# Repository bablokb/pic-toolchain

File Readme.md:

PIC Toolchain
=============

This is a collection of notes, sources and tools for a complete
PIC toolchain for the Raspbian operating-system.

Toolset
=======

To compile, link and flash PIC code, you need on software-side

  - a compiler (SDCC)
  - an assembler and linker (gputils)
  - a flasher

The first two programs are available for Raspbian, but it is recommended
to build both programs from source. For flashing, you need the 
program `pk2cmd`. You can find a precompiled version for armv6l in
`files/usr/local/bin`.

Example Programs
================

The directory `projects` contains a number of sample projects.
You must copy (install) the rule-files `projects/ptc_rules*.inc`
(generic makefile-rules) to a system-include directory automatically
searched by `make`, e.g. `/usr/local/include` or add the `-I dir` option
to the invocation of `make`.

The directory `projects/include` contains `.h`-files (c-includes)
used by all projects. You should also copy (install) these files to
`/usr/local/include` if you want to use these files in other projects.

The projects demonstrate various aspects, e.g. how to embbed assembler code
into C-code, or link with preexisting assembler-code.

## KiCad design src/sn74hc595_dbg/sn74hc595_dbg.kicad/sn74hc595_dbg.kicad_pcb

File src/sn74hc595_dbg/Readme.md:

SN74HC595 based debugger for the PIC12F675
==========================================

This project has moved to [https://github.com/bablokb/pic-sn74hc595](https://github.com/bablokb/pic-sn74hc595).

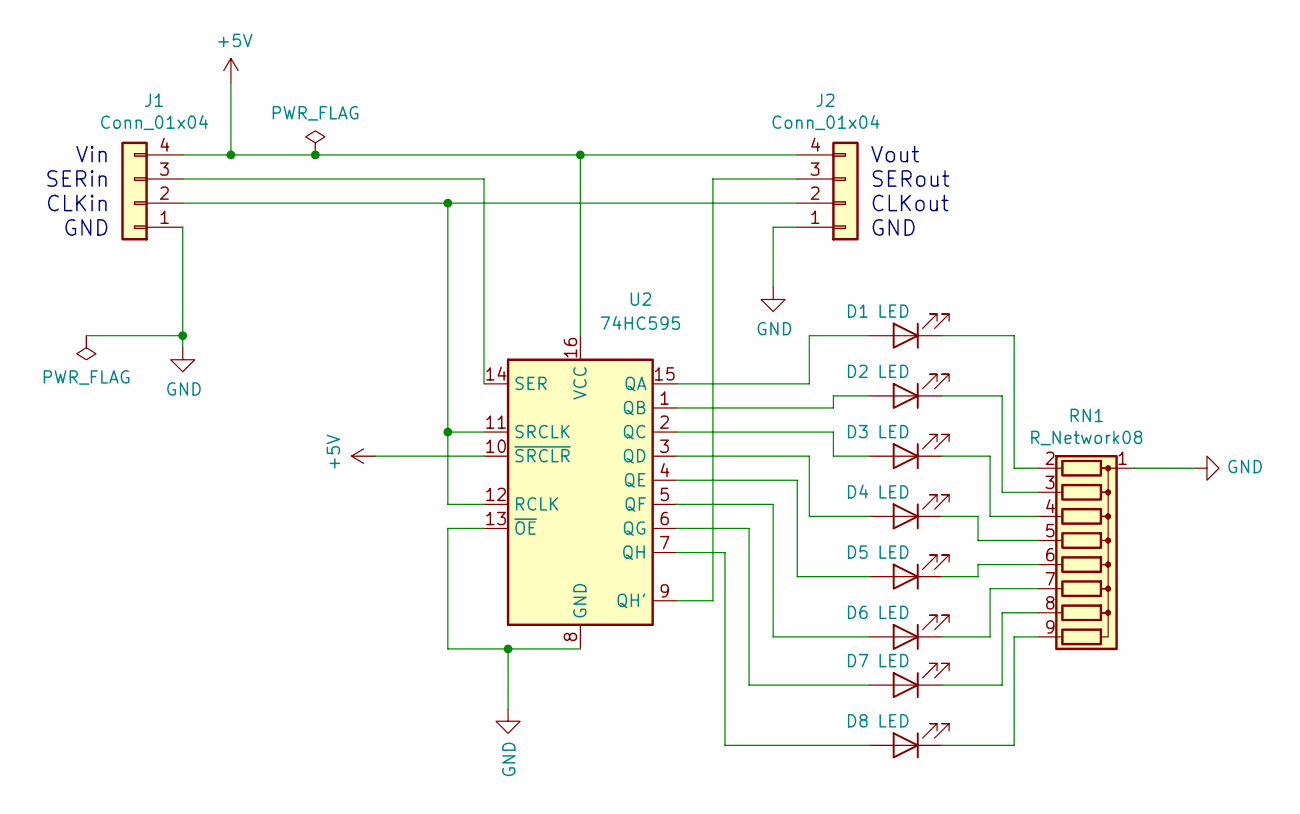
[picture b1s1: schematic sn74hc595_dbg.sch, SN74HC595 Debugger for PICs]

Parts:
D1, D2, D3, D4, D5, D6, D7, D8: LED; LED_D3.0mm
J1, J2: Conn_01x04; PinHeader_1x04_P2.54mm_Vertical
RN1: R_Network08; R_Array_SIP9
U2: 74HC595; DIP-16_W7.62mm_Socket

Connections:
+5V: J1.4, J2.4, U2.10 (~SRCLR), U2.16 (VCC)
GND: J1.1, J2.1, RN1.1 (common), U2.8 (GND), U2.13 (~OE)
unnamed: D1.1 (K), RN1.2 (R1)
unnamed: D1.2 (A), U2.15 (QA)
unnamed: D2.1 (K), RN1.3 (R2)
unnamed: D2.2 (A), U2.1 (QB)
unnamed: D3.1 (K), RN1.4 (R3)
unnamed: D3.2 (A), U2.2 (QC)
unnamed: D4.1 (K), RN1.5 (R4)
unnamed: D4.2 (A), U2.3 (QD)
unnamed: D5.1 (K), RN1.6 (R5)
unnamed: D5.2 (A), U2.4 (QE)
unnamed: D6.1 (K), RN1.7 (R6)
unnamed: D6.2 (A), U2.5 (QF)
unnamed: D7.1 (K), RN1.8 (R7)
unnamed: D7.2 (A), U2.6 (QG)
unnamed: D8.1 (K), RN1.9 (R8)
unnamed: D8.2 (A), U2.7 (QH)
unnamed: J1.2, J2.2, U2.11 (SRCLK), U2.12 (RCLK)
unnamed: J1.3, U2.14 (SER)
unnamed: J2.3, U2.9 (QH')

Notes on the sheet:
Vin SERin CLKin GND
Vout SERout CLKout GND

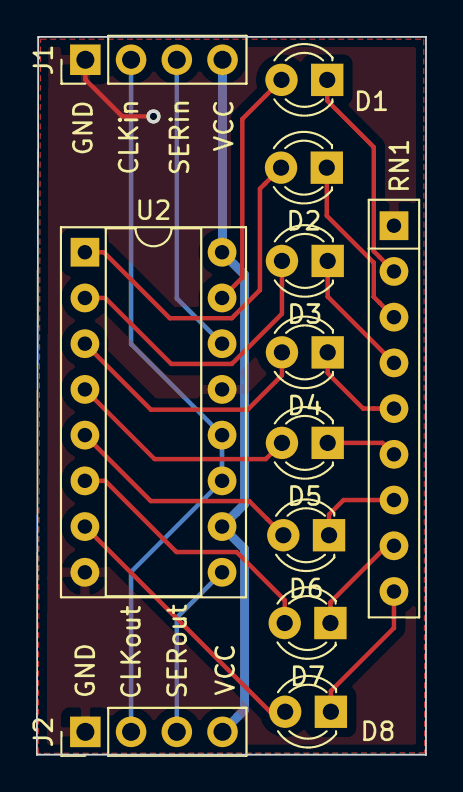
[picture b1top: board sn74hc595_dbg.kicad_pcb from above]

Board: 2 copper layers, 21.6 x 39.9 mm, 12 parts (0 on the bottom side), 21 nets.

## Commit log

2018-12-15 initial entry
2018-12-22 added clrwdt, not_gppu and cmcon
2018-12-24 added bank-switching to OSCCAL configuration
2018-12-24 added bank-switching to OSCCAL configuration (plus some code reordering)
2018-12-29 changed comments to English
2018-12-30 changed build-comment
2018-12-30 also remove *.map and *.hex during clean
2019-01-05 added note about not sleeping in maiin
2019-01-05 support EXTRA_C variable
2019-01-10 moved targets to top / fix clean command
2019-01-10 send crlf instead of lf
2019-01-11 reverting last change - leave conversion to terminal-application
2019-01-11 new function softuart_print()
2019-01-11 use new function softuart_print()
2019-01-11 don't only echo character back, but print additional stuff
2019-01-15 removed
2020-02-24 removed notes
2020-02-28 refactoring, fixes etc.
2020-02-29 bugfix: don't clear all interrupt-bits within ISR
2020-02-29 added some details
2020-03-08 ignore any interrupts for 5 seconds after turning on power
2020-03-08 document wait after power-on
2020-03-08 fix info about gpio-shutdown
2020-03-12 bugfix: power is on if gate is low
2020-03-20 suppress warnings of gpasm
2020-03-21 Rev 2: replaced LCD-component (to match pin-order)
2020-03-21 added write to second line
2020-03-21 repeat init-sequence 3 times
2020-03-21 tie VO to GND for better contrast
2020-03-21 changed variable names from LCD_ to PIN_
2020-03-21 minor improvements
2020-03-21 various changes
2020-03-21 removed lcd_enable()
2020-03-21 Rev 4: wire backlight pins 15 and 16
2020-03-21 tie VO to GND (increase contrast), wire backlight pins 15 and 16
2020-03-21 use init-sequence for 4-bit mode
2020-03-26 bugfix: delay_ms used count instead of count2
2020-03-26 indent text to position 4
2020-03-26 bugfix: switch to 4-bit mode
2020-03-26 Rev 5: added variable resistor for VO
2020-03-26 added variable resistor for VO
2020-03-28 minor changes to header
2020-03-28 renamed lcd_write_byte() to lcd_shift_out()
2020-03-29 replaced lcd_clear() with a macro
2020-03-31 added poti for VO
2020-03-31 added annotations
2020-04-02 removed empty boarders
2020-04-03 fixed power-connector
2020-04-19 Rev 1: initial commit
2020-04-20 swapped horizontal LEDs with vertical LEDs
2020-04-20 optimized layout, added labels
2020-04-29 additional argument SDCC_ARGS for sdcc
2020-05-04 point to new location of project
2020-05-04 removed files (moved to dedicated project)
2020-05-04 added lcd_print_i() and lcd_print_x()
2020-05-10 moved directory to dedicated project
2020-05-10 replaced content with link of new dedicated project
2020-10-25 target flash: use pkcmd-lx (old target flash now flash2)
2020-10-25 use sdcc for linking
2020-10-26 added note about package name within OpenSuse
2020-10-29 try to autodetect MODEL if not provided
2020-10-29 migrate to auto-configuration
2020-10-29 make GP for led configurable
2020-10-30 moved to include-directory
2020-10-30 include alias_xxx.h from include/ (don't create it)
2020-10-30 renamed directory 'src' to 'projects'
2020-10-30 updated name of directory for projects
2020-10-30 make MCLR configurable
2020-11-01 create alias.inc / remove HEXF
2020-11-02 not necessary to set INTEDG
2020-11-05 pass CPPFLAGS and CFLAGS to sdcc
2020-11-15 renamed files alias_*->picconfig_*
2020-11-15 include picconfig.h/picconfig.inc instead of alias.h/alias.inc
2020-11-16 include pic14regs.h from picconfig_* if SDCC is the compiler
2020-11-16 move include of pic14regs.h to picconfig_*
2020-11-16 added support for PIC12F1612
2020-12-23 defined macros INIT_SPECIAL and CLOCK_4MHZ
2020-12-23 use new macros
2020-12-23 added defines for bitset/bitclear
2020-12-23 use new bitset macro
2020-12-24 added macro bitread
2020-12-24 refactored SDCC-specific stuff to rules_sdcc.inc
2020-12-26 renamed rules*.inc to ptc_rules*.inc
2020-12-26 rename bitclr to bitclear
2020-12-26 add /usr/local/include to SDCC include search path
2020-12-26 document need to install rules and include-files for pic-toolchain
2020-12-28 bugfix: tested wrong variable for goal
2021-01-03 refactor MCLR-config to ptc_rules_xxx.inc
2021-01-03 initial implementation
2021-01-03 added missing macros for xc8
2021-01-03 add xc8 support
2021-01-03 changed inline asm-code for xc8-compatibility
2021-01-03 include toolchain-specific rules from tc.mk
2021-01-03 clean: also remove tc.mk
2021-01-03 remove all intermediate files of xc8
2021-01-03 updated value of MCLR-variable to match new scheme
2021-01-03 migrated to picconfig-standard
2021-01-03 refactored common code to picconfig_default.h
2021-01-03 map xc8 asm() to sdcc __asm__() if sdcc is in use
2021-01-04 fixed pragma config
2021-01-08 map more identifiers between xc8 and sdcc
2021-01-08 change include-statement
2021-01-08 added : to labels
2021-01-08 changed file-encoding
2021-01-08 migrate to pic-as (xc8-assember)
2021-01-08 fix handling of asm-source files
2021-01-08 captitalize psect
2021-01-08 refactor target picconfig.inc to toolchain-specific rule-files
2021-01-08 implement target picconfig.inc to support toolchain-agnostic asm-files
2021-01-09 include picconfig.h instead of pic12f675.h
2021-01-10 fix: #include "picconfig.h" instead of <picconfig.h>
2021-01-10 removed include of pic12f675.h
2021-01-10 minor changes for xc8-compatibility
2021-01-10 compile to .p1 instead of .obj
2021-01-12 don't set MODEL
2021-01-12 migrate to standard
2021-01-14 define __CHIPNAME for sdcc to be xc8 compatible
2021-02-07 added target config
2021-02-07 split target clean into clean and distclean (clean preserves config)
2021-02-07 remove trailing semicolon from #define of CONFIG_WORDS
2021-03-13 define IOC-macros and constants
2021-03-13 migrated to IOC-macros
2021-03-13 changed default for PIN_ON to 0
2021-03-20 refactored #defines for pin-names: use modern RA-based chips as basis instead GP-based chips
2021-03-20 replaced CMCON with CM1CON0
2021-03-21 replaced WPU with WPUA
2021-03-21 replaced IOC-related variables
2021-03-21 don't set unneeded variables
2021-03-22 added option '-I.' to compile-commands
2021-04-05 create map-file during linking
2021-04-30 define _PTC
2021-07-28 added PORTAbits
2021-07-28 fixed pragmas (preprocessor does not replace values)
